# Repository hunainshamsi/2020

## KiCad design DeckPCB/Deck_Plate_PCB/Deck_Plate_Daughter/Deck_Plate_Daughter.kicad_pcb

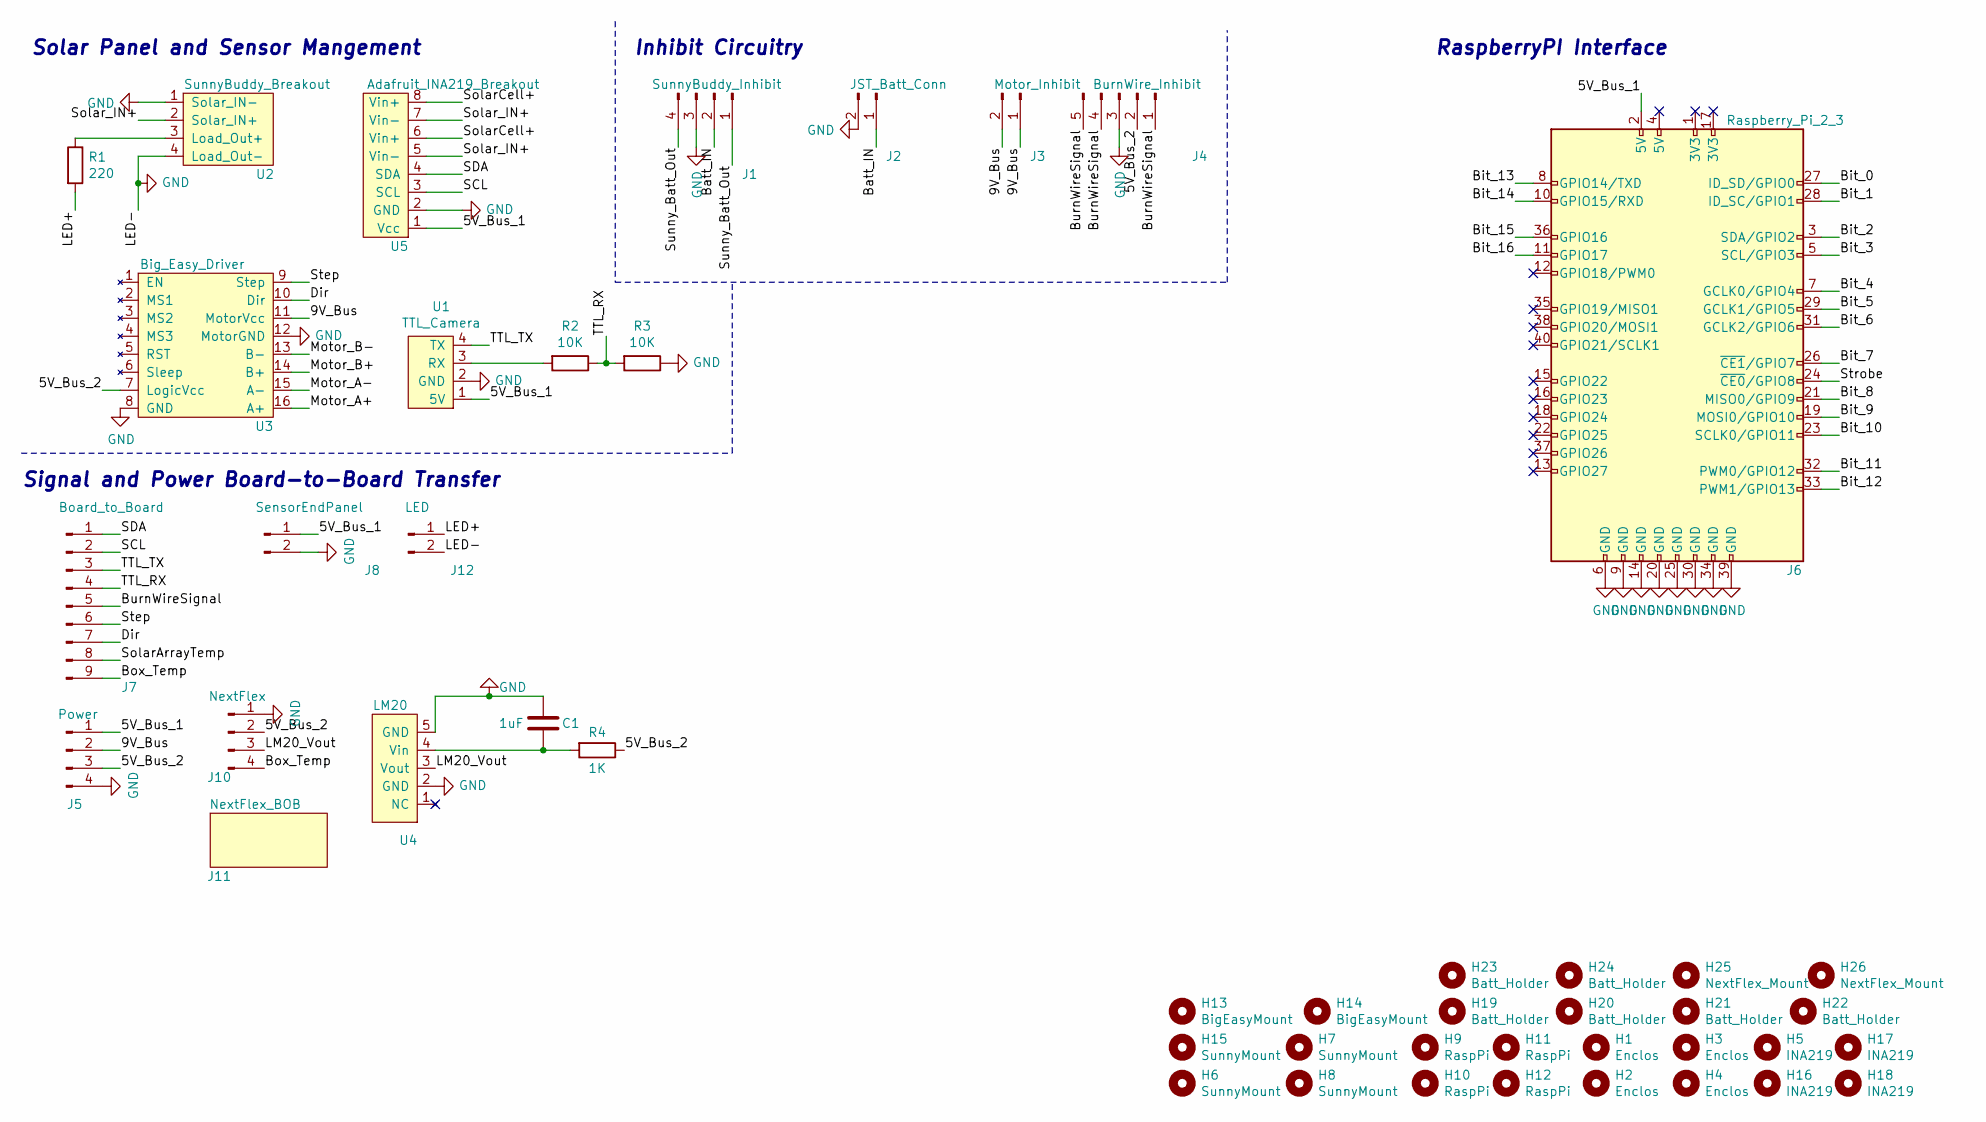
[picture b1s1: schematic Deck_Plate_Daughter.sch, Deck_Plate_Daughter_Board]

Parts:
C1: 1uF; C_Axial_L3.8mm_D2.6mm_P7.50mm_Horizontal
H1, H2, H3, H4: Enclos; MountingHole_3.5mm
H5, H16, H17, H18: INA219; Accel_MountingHole_2.5mm
H6, H7, H8, H15: SunnyMount; Accel_MountingHole_2.5mm
H9, H10, H11, H12: RaspPi; MountingHole_2.5mm
H13, H14: BigEasyMount; BigEasy_MountingHole_3.2mm_M3
H19, H20, H21, H22, H23, H24: Batt_Holder; MountingHole_5.3mm_M5
H25, H26: NextFlex_Mount; NextFlex_Mount_3mm
J1: SunnyBuddy_Inhibit; PinHeader_1x04_P2.54mm_Vertical
J2: JST_Batt_Conn; JST_PH_B2B-PH-K_1x02_P2.00mm_Vertical
J3: Motor_Inhibit; PinHeader_1x02_P2.54mm_Vertical
J4: BurnWire_Inhibit; PinHeader_1x05_P2.54mm_Vertical
J5: Power; PinHeader_1x04_P2.54mm_Vertical
J6: Raspberry_Pi_2_3; PinHeader_2x20_P2.54mm_Vertical
J7: Board_to_Board; PinHeader_1x09_P2.54mm_Vertical
J8: SensorEndPanel; PinHeader_1x02_P2.54mm_Vertical
J10: NextFlex; PinHeader_1x04_P2.54mm_Vertical
J11: NextFlex_BOB; NextFlex
J12: LED; PinHeader_1x02_P2.54mm_Vertical
R1: 220; R_Axial_DIN0207_L6.3mm_D2.5mm_P10.16mm_Horizontal
R2, R3: 10K; R_Axial_DIN0207_L6.3mm_D2.5mm_P10.16mm_Horizontal
R4: 1K; R_Axial_DIN0207_L6.3mm_D2.5mm_P10.16mm_Horizontal
U1: TTL_Camera; PinHeader_1x04_P2.54mm_Vertical
U2: SunnyBuddy_Breakout
U3: Big_Easy_Driver
U4: LM20; SOT-353_SC-70-5_Handsoldering
U5: Adafruit_INA219_Breakout; Adafruit_INA219_Breakout_header

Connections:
/5V_Bus_1: J5.1, J6.2 (5V), J8.1, U1.1 (5V), U5.1 (Vcc)
/5V_Bus_2: J4.2, J5.3, J10.2, R4.1, U3.7 (LogicVcc)
/9V_Bus: J3.1, J3.2, J5.2, U3.11 (MotorVcc)
/Batt_IN: J1.2, J2.1
/Bit_0: J6.27 (ID_SD/GPIO0)
/Bit_1: J6.28 (ID_SC/GPIO1)
/Bit_2: J6.3 (SDA/GPIO2)
/Bit_3: J6.5 (SCL/GPIO3)
/Bit_4: J6.7 (GCLK0/GPIO4)
/Bit_5: J6.29 (GCLK1/GPIO5)
/Bit_6: J6.31 (GCLK2/GPIO6)
/Bit_7: J6.26 (~CE1~/GPIO7)
/Bit_8: J6.21 (MISO0/GPIO9)
/Bit_9: J6.19 (MOSI0/GPIO10)
/Bit_10: J6.23 (SCLK0/GPIO11)
/Bit_11: J6.32 (PWM0/GPIO12)
/Bit_12: J6.33 (PWM1/GPIO13)
/Bit_13: J6.8 (GPIO14/TXD)
/Bit_14: J6.10 (GPIO15/RXD)
/Bit_15: J6.36 (GPIO16)
/Bit_16: J6.11 (GPIO17)
/Box_Temp: J7.9, J10.4
/BurnWireSignal: J4.1, J4.4, J4.5, J7.5
/Dir: J7.7, U3.10 (Dir)
/LED+: J12.1, R1.2
/LM20_Vout: J10.3, U4.3 (Vout)
/Motor_A+: U3.16 (A+)
/Motor_A-: U3.15 (A-)
/Motor_B+: U3.14 (B+)
/Motor_B-: U3.13 (B-)
/SCL: J7.2, U5.3 (SCL)
/SDA: J7.1, U5.4 (SDA)
/SolarArrayTemp: J7.8
/SolarCell+: U5.6 (Vin+), U5.8 (Vin+)
/Solar_IN+: U2.2 (Solar_IN+), U5.5 (Vin-), U5.7 (Vin-)
/Step: J7.6, U3.9 (Step)
/Strobe: J6.24 (~CE0~/GPIO8)
/Sunny_Batt_Out: J1.1, J1.4
/TTL_RX: J7.4, R2.1, R3.2
/TTL_TX: J7.3, U1.4 (TX)
GND: C1.2, J1.3, J2.2, J4.3, J5.4, J6.6 (GND), J6.9 (GND), J6.14 (GND), J6.20 (GND), J6.25 (GND), J6.30 (GND), J6.34 (GND), J6.39 (GND), J8.2, J10.1, J12.2, R3.1, U1.2 (GND), U2.1 (Solar_IN-), U2.4 (Load_Out-), U3.8 (GND), U3.12 (MotorGND), U4.2 (GND), U4.5 (GND), U5.2 (GND)
unnamed: C1.1, R4.2, U4.4 (Vin)
unnamed: R1.1, U2.3 (Load_Out+)
unnamed: R2.2, U1.3 (RX)

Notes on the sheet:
Inhibit Circuitry
Solar Panel and Sensor Mangement
Signal and Power Board-to-Board Transfer
RaspberryPI Interface

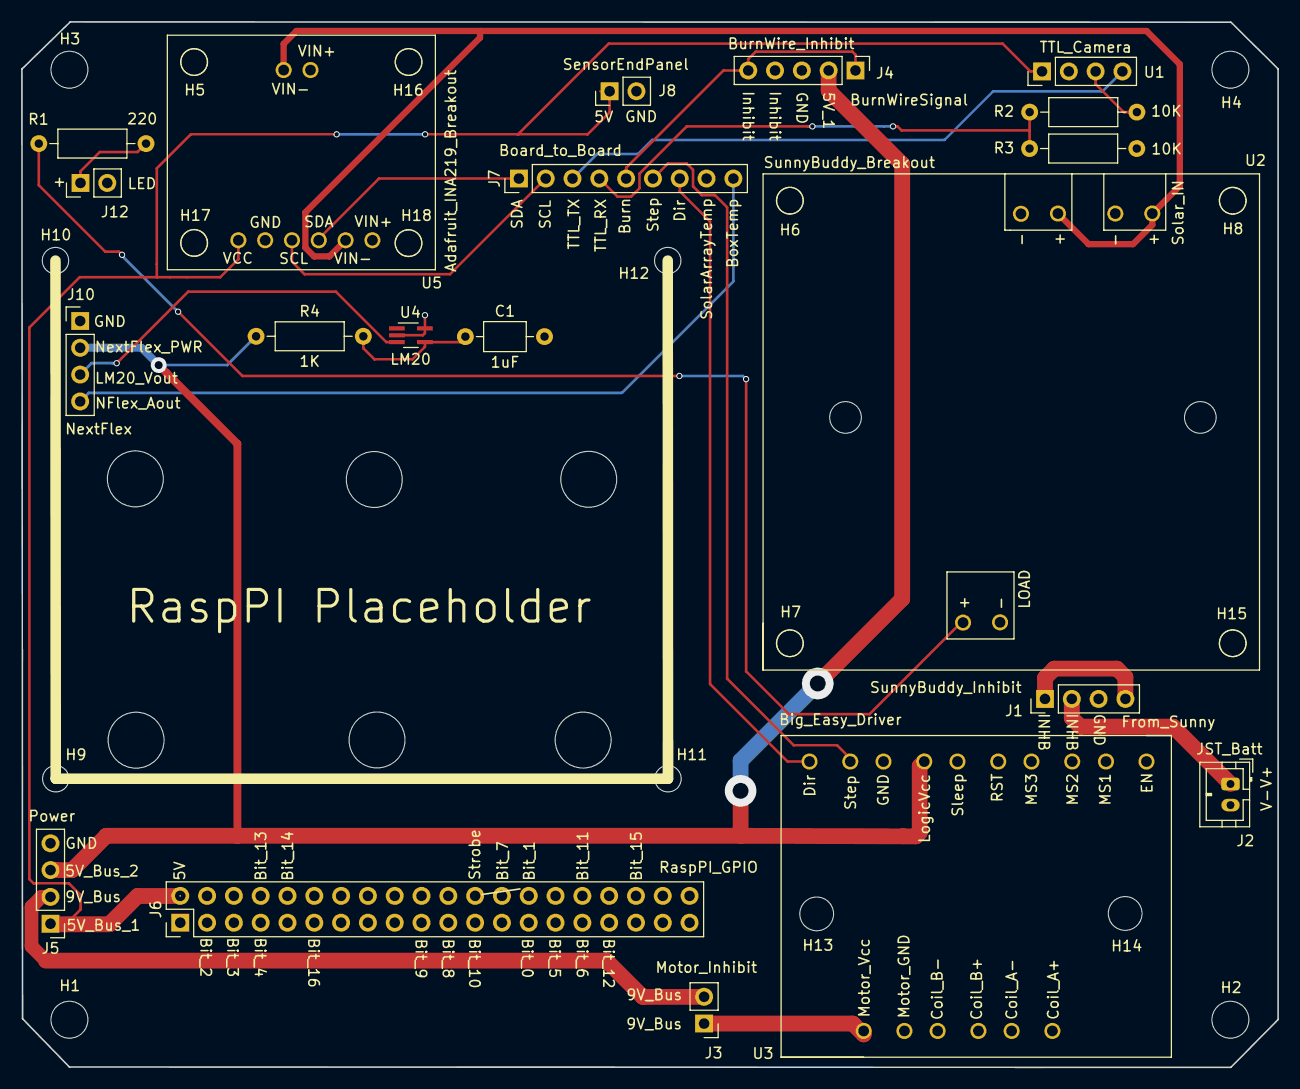
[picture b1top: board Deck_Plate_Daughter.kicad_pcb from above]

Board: 2 copper layers, 119.0 x 99.1 mm, 47 parts (0 on the bottom side), 21 nets.

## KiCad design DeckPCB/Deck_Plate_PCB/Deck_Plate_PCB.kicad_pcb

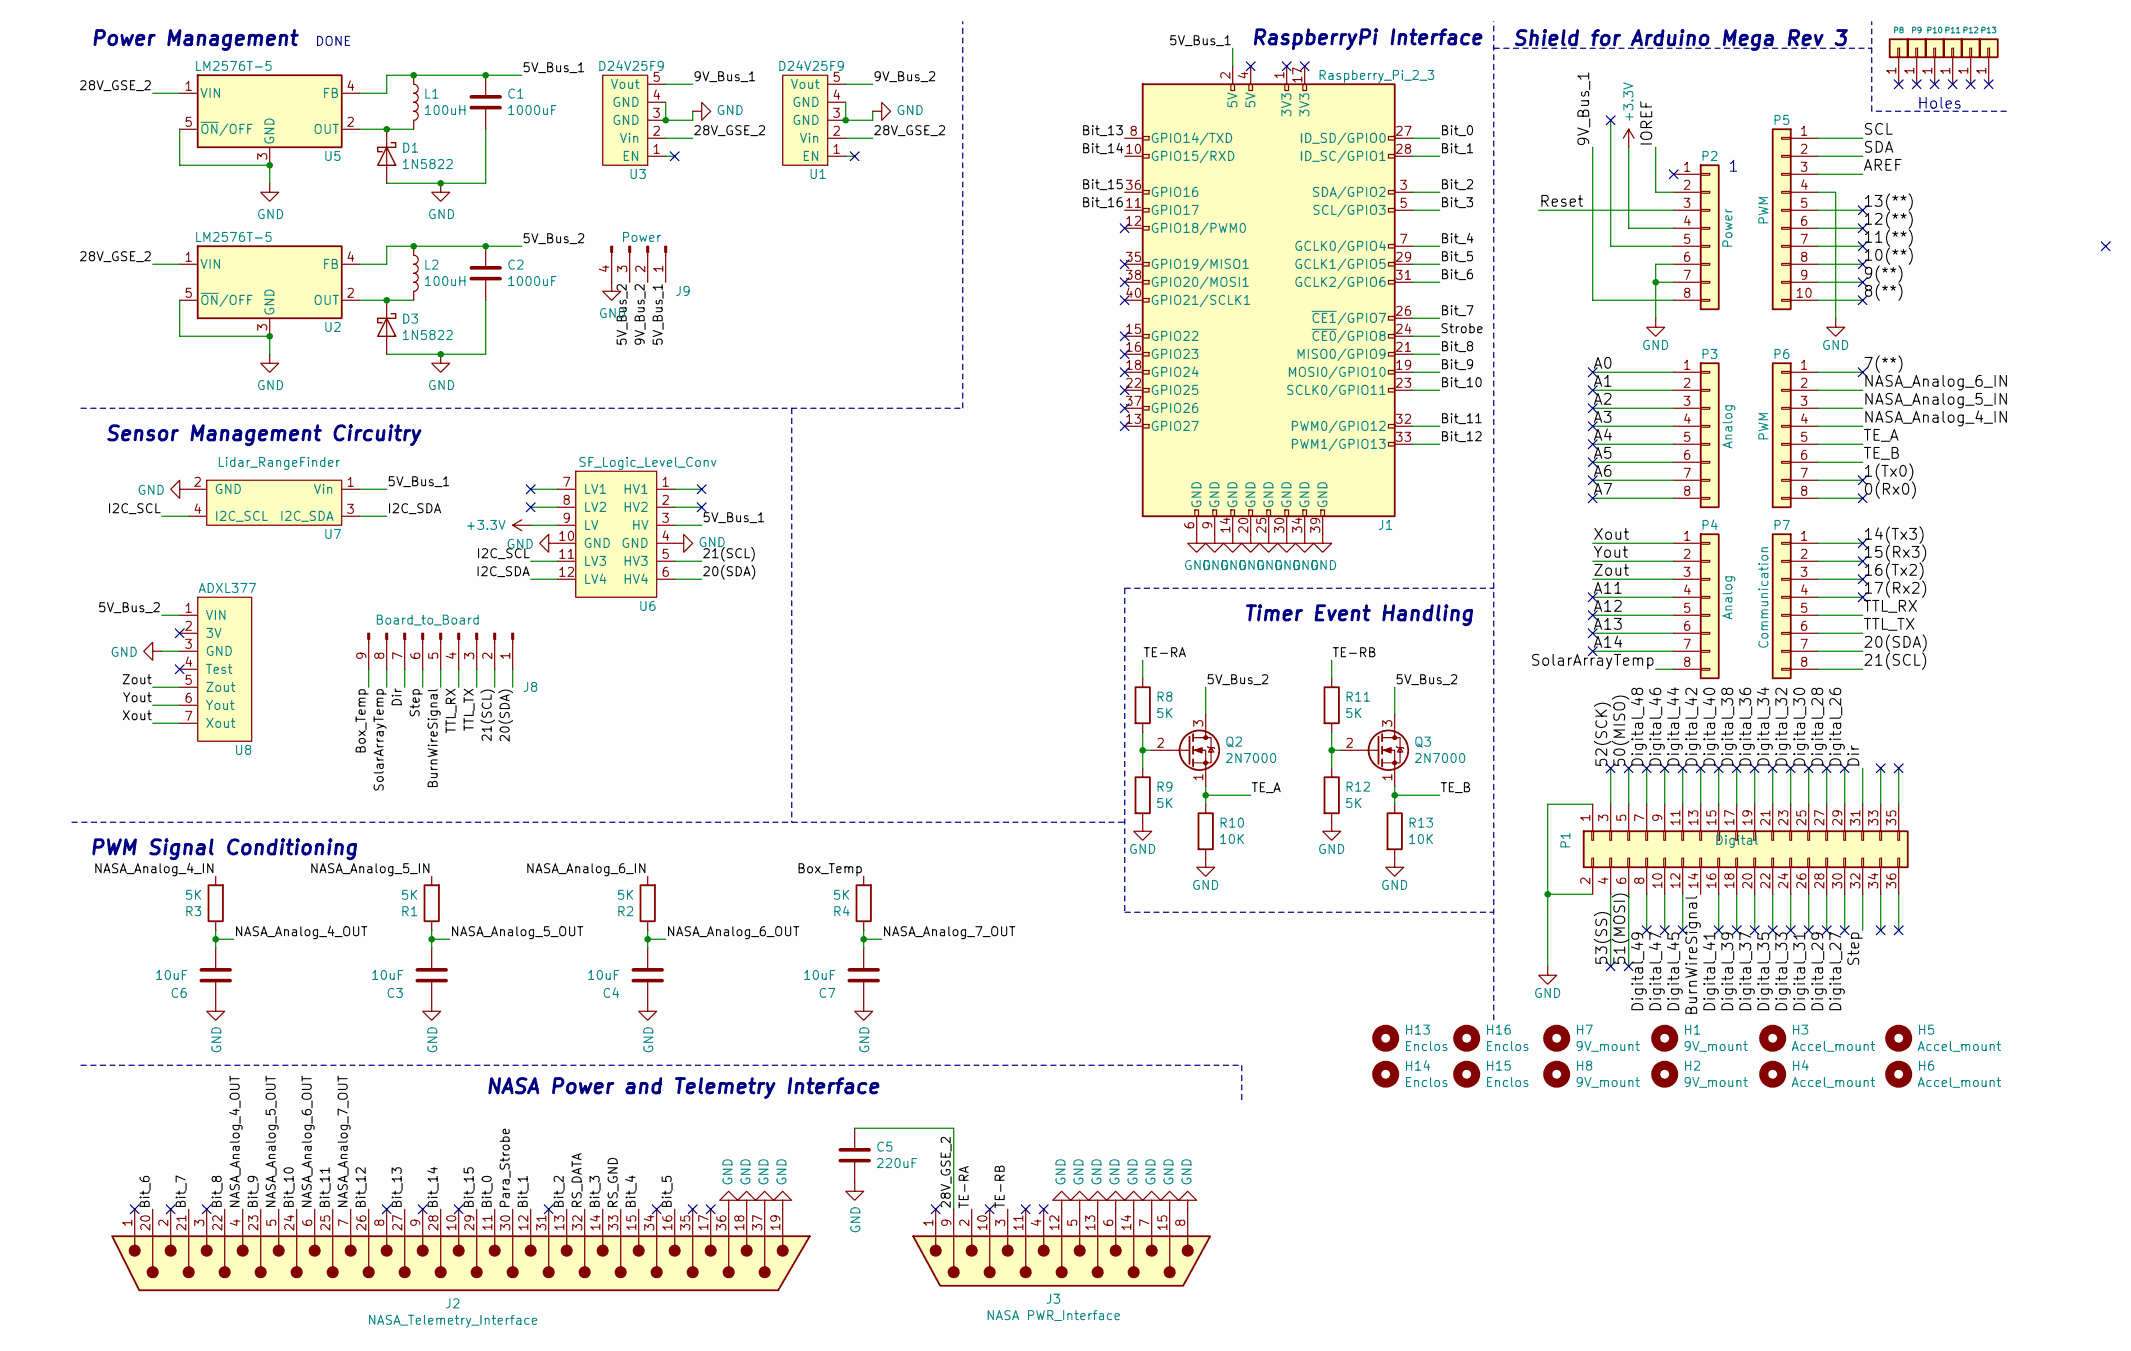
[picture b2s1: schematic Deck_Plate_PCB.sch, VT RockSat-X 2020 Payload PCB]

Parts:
C1, C2: 1000uF; 1000uF_Cap
C3, C4, C6, C7: 10uF; C_Axial_L3.8mm_D2.6mm_P7.50mm_Horizontal; Manufacture P/N FG24X7R1A106KRT06; DigiKey P/N 445-173370-1-ND
C5: 220uF; 220uF_Cap
D1, D3: 1N5822; D_DO-201AD_P12.70mm_Horizontal
H1, H2, H7, H8: 9V_mount; 9V_MountingHole_2.2mm
H3, H4, H5, H6: Accel_mount; Accel_MountingHole_2.5mm
H13, H14, H15, H16: Enclos; MountingHole_3.5mm
J1: Raspberry_Pi_2_3; PinHeader_2x20_P2.54mm_Vertical
J2: NASA_Telemetry_Interface; NASA_Telem_37-pin_DSub
J3: NASA PWR_Interface; NASA_PWR_15-pin_DSub
J8: Board_to_Board; PinHeader_1x09_P2.54mm_Vertical
J9: Power; PinHeader_1x04_P2.54mm_Vertical
L1, L2: 100uH; L_Toroid_Vertical_L21.6mm_W9.5mm_P7.11mm_Pulse_C
P1: Digital; Socket_Strip_Arduino_2x18
P2: Power; Socket_Strip_Arduino_1x08
P3, P4: Analog; Socket_Strip_Arduino_1x08
P5: PWM; Socket_Strip_Arduino_1x10
P6: PWM; Socket_Strip_Arduino_1x08
P7: Communication; Socket_Strip_Arduino_1x08
P8, P9, P10, P11, P12, P13: CONN_01X01; Arduino_1pin
Q2, Q3: 2N7000; TO-92_Inline
R1, R2, R3, R4, R8, R9, R11, R12: 5K; R_Axial_DIN0207_L6.3mm_D2.5mm_P10.16mm_Horizontal
R10, R13: 10K; R_Axial_DIN0207_L6.3mm_D2.5mm_P10.16mm_Horizontal; Manufacture P/N RNF14FTD10K0; DigiKey P/N RNF14FTD10K0CT-ND
U1, U3: D24V25F9
U2, U5: LM2576T-5; TO-220-5_Vertical
U6: SF_Logic_Level_Conv
U7: Lidar_RangeFinder; PinHeader_1x04_P2.54mm_Vertical
U8: ADXL377; ADXL337

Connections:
+3V3: P2.4, U6.9 (LV)
/0(Rx0): P6.8
/1(Tx0): P6.7
/5V_Bus_1: C1.1, J1.2 (5V), J9.1, L1.1, U5.4 (FB), U6.3 (HV), U7.1 (Vin)
/5V_Bus_2: C2.1, J9.3, L2.1, Q2.3 (D), Q3.3 (D), U2.4 (FB), U8.1 (VIN)
/7(**): P6.1
/8(**): P5.10
/9(**): P5.9
/9V_Bus_1: P2.8, U3.5 (Vout)
/9V_Bus_2: J9.2, U1.5 (Vout)
/10(**): P5.8
/11(**): P5.7
/12(**): P5.6
/13(**): P5.5
/14(Tx3): P7.1
/15(Rx3): P7.2
/16(Tx2): P7.3
/17(Rx2): P7.4
/20(SDA): J8.1, P7.7, U6.6 (HV4)
/21(SCL): J8.2, P7.8, U6.5 (HV3)
/28V_GSE_2: C5.1, J3.9, U1.2 (Vin), U2.1 (VIN), U3.2 (Vin), U5.1 (VIN)
/50(MISO): P1.5
/51(MOSI): P1.6
/52(SCK): P1.3
/53(SS): P1.4
/A0: P3.1
/A1: P3.2
/A2: P3.3
/A3: P3.4
/A4: P3.5
/A5: P3.6
/A6: P3.7
/A7: P3.8
/A11: P4.4
/A12: P4.5
/A13: P4.6
/A14: P4.7
/AREF: P5.3
/Bit_0: J1.27 (ID_SD/GPIO0), J2.11
/Bit_1: J1.28 (ID_SC/GPIO1), J2.12
/Bit_2: J1.3 (SDA/GPIO2), J2.13
/Bit_3: J1.5 (SCL/GPIO3), J2.14
/Bit_4: J1.7 (GCLK0/GPIO4), J2.15
/Bit_5: J1.29 (GCLK1/GPIO5), J2.16
/Bit_6: J1.31 (GCLK2/GPIO6), J2.20
/Bit_7: J1.26 (~CE1~/GPIO7), J2.21
/Bit_8: J1.21 (MISO0/GPIO9), J2.22
/Bit_9: J1.19 (MOSI0/GPIO10), J2.23
/Bit_10: J1.23 (SCLK0/GPIO11), J2.24
/Bit_11: J1.32 (PWM0/GPIO12), J2.25
/Bit_12: J1.33 (PWM1/GPIO13), J2.26
/Bit_13: J1.8 (GPIO14/TXD), J2.27
/Bit_14: J1.10 (GPIO15/RXD), J2.28
/Bit_15: J1.36 (GPIO16), J2.29
/Bit_16: J1.11 (GPIO17)
/Box_Temp: J8.9, R4.2
/BurnWireSignal: J8.5, P1.14
/Digital_26: P1.29
/Digital_27: P1.30
/Digital_28: P1.27
/Digital_29: P1.28
/Digital_30: P1.25
/Digital_31: P1.26
/Digital_32: P1.23
/Digital_33: P1.24
/Digital_34: P1.21
/Digital_35: P1.22
/Digital_36: P1.19
/Digital_37: P1.20
/Digital_38: P1.17
/Digital_39: P1.18
/Digital_40: P1.15
/Digital_41: P1.16
/Digital_42: P1.13
/Digital_44: P1.11
/Digital_45: P1.12
/Digital_46: P1.9
/Digital_47: P1.10
/Digital_48: P1.7
/Digital_49: P1.8
/Dir: J8.7, P1.31
/I2C_SCL: U6.11 (LV3), U7.4 (I2C_SCL)
/I2C_SDA: U6.12 (LV4), U7.3 (I2C_SDA)
/IOREF: P2.2
/NASA_Analog_4_IN: P6.4, R3.2
/NASA_Analog_4_OUT: C6.2, J2.4, R3.1
/NASA_Analog_5_IN: P6.3, R1.2
/NASA_Analog_5_OUT: C3.2, J2.5, R1.1
/NASA_Analog_6_IN: P6.2, R2.2
/NASA_Analog_6_OUT: C4.2, J2.6, R2.1
/NASA_Analog_7_OUT: C7.2, J2.7, R4.1
/Para_Strobe: J2.30
/RS_DATA: J2.32
/RS_GND: J2.33
/Reset: P2.3
/SCL: P5.1
/SDA: P5.2
/SolarArrayTemp: J8.8, P4.8
/Step: J8.6, P1.32
/Strobe: J1.24 (~CE0~/GPIO8)
/TE-RA: J3.2, R8.1
/TE-RB: J3.3, R11.1
/TE_A: P6.5, Q2.1 (S), R10.1
/TE_B: P6.6, Q3.1 (S), R13.1
/TTL_RX: J8.4, P7.5
/TTL_TX: J8.3, P7.6
/Xout: P4.1, U8.7 (Xout)
/Yout: P4.2, U8.6 (Yout)
/Zout: P4.3, U8.5 (Zout)
GND: C1.2, C2.2, C3.1, C4.1, C5.2, C6.1, C7.1, D1.2 (A), D3.2 (A), J1.6 (GND), J1.9 (GND), J1.14 (GND), J1.20 (GND), J1.25 (GND), J1.30 (GND), J1.34 (GND), J1.39 (GND), J2.18, J2.19, J2.36, J2.37, J3.5, J3.6, J3.7, J3.8, J3.12, J3.13, J3.14, J3.15, J9.4, P1.1, P1.2, P2.6, P2.7, P5.4, R9.2, R10.2, R12.2, R13.2, U1.3 (GND), U1.4 (GND), U2.3 (GND), U2.5 (~ON~/OFF), U3.3 (GND), U3.4 (GND), U5.3 (GND), U5.5 (~ON~/OFF), U6.4 (GND), U6.10 (GND), U7.2 (GND), U8.3 (GND)
unnamed: D1.1 (K), L1.2, U5.2 (OUT)
unnamed: D3.1 (K), L2.2, U2.2 (OUT)
unnamed: Q2.2 (G), R8.2, R9.1
unnamed: Q3.2 (G), R11.2, R12.1

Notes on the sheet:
Shield for Arduino Mega Rev 3
Holes
Power Management
Sensor Management Circuitry
NASA Power and Telemetry Interface
Timer Event Handling
DONE
RaspberryPi Interface
PWM Signal Conditioning

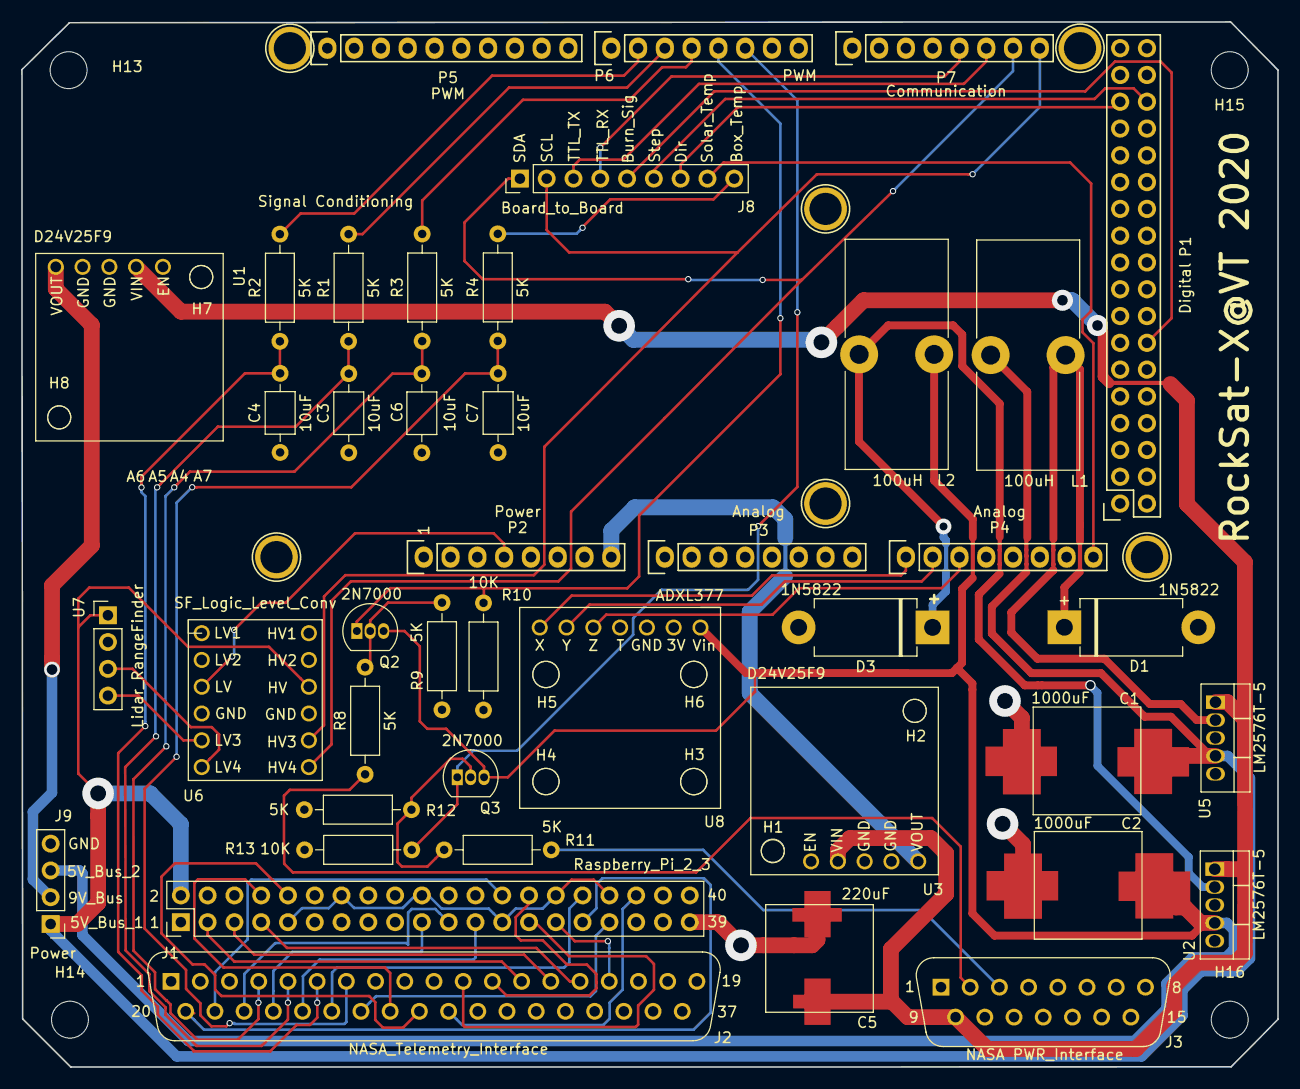
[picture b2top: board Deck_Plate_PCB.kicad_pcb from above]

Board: 2 copper layers, 119.1 x 99.1 mm, 60 parts (0 on the bottom side), 52 nets.

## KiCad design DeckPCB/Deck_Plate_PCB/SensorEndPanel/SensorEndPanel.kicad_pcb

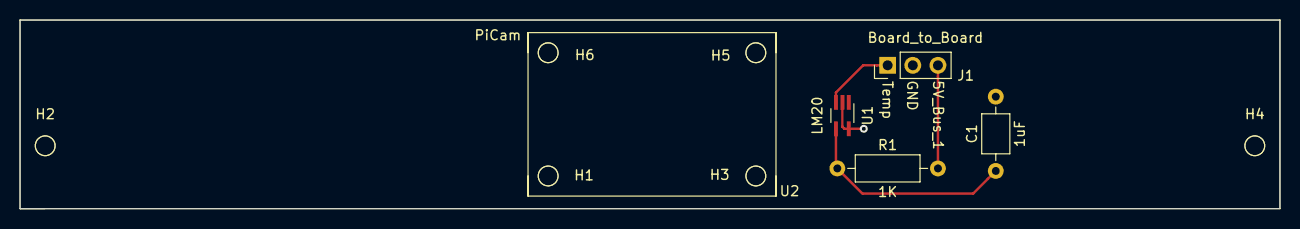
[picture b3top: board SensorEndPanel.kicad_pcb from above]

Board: 2 copper layers, 127.3 x 19.1 mm, 11 parts (0 on the bottom side), 4 nets.

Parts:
C1: 1uF; C_Axial_L3.8mm_D2.6mm_P7.50mm_Horizontal
H1, H2, H3, H4, H5, H6: MountingHole; MountingHole_2mm
J1: Board_to_Board; PinHeader_1x03_P2.54mm_Vertical
R1: 1K; R_Axial_DIN0207_L6.3mm_D2.5mm_P10.16mm_Horizontal
U1: LM20; SOT-353_SC-70-5_Handsoldering
U2: PiCam

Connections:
/5V_Bus_1: J1.3, R1.2
/SolarArrayTemp: J1.1, U1.3
GND: C1.2, J1.2, U1.2, U1.5
unnamed: C1.1, R1.1, U1.4

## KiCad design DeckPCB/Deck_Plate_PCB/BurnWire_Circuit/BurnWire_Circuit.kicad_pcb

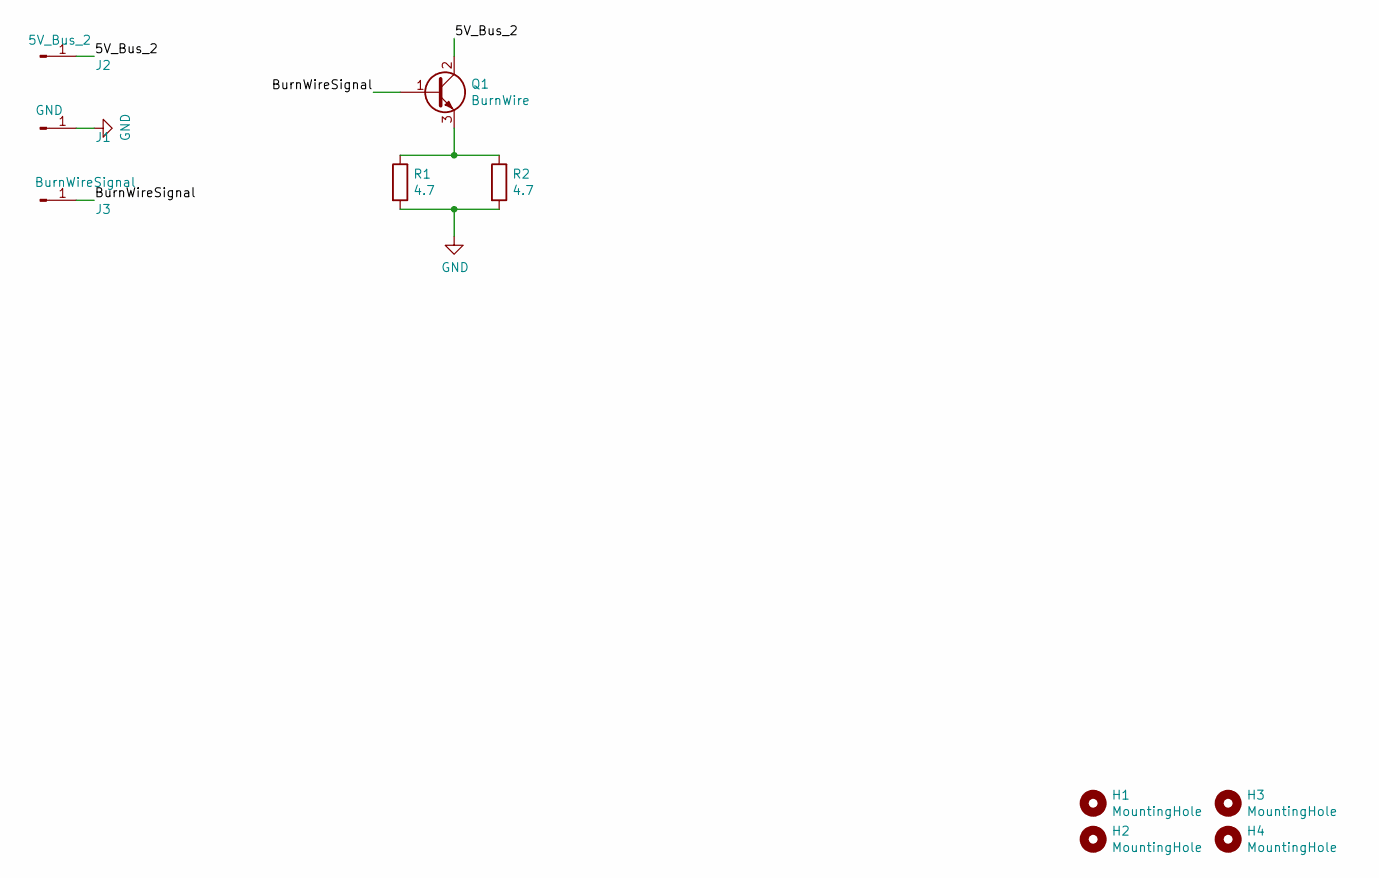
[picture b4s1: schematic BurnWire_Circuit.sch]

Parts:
H1, H2, H3, H4: MountingHole; MountingHole_3.2mm_M3
J1: GND; Terminal_Lug_PCB
J2: 5V_Bus_2; Terminal_Lug_PCB
J3: BurnWireSignal; Terminal_Lug_PCB
Q1: BurnWire; TO-251-3_Vertical
R1, R2: 4.7; R_Axial_DIN0207_L6.3mm_D2.5mm_P10.16mm_Horizontal

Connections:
/5V_Bus_2: J2.1, Q1.2 (C)
/BurnWireSignal: J3.1, Q1.1 (B)
GND: J1.1, R1.2, R2.2
unnamed: Q1.3 (E), R1.1, R2.1

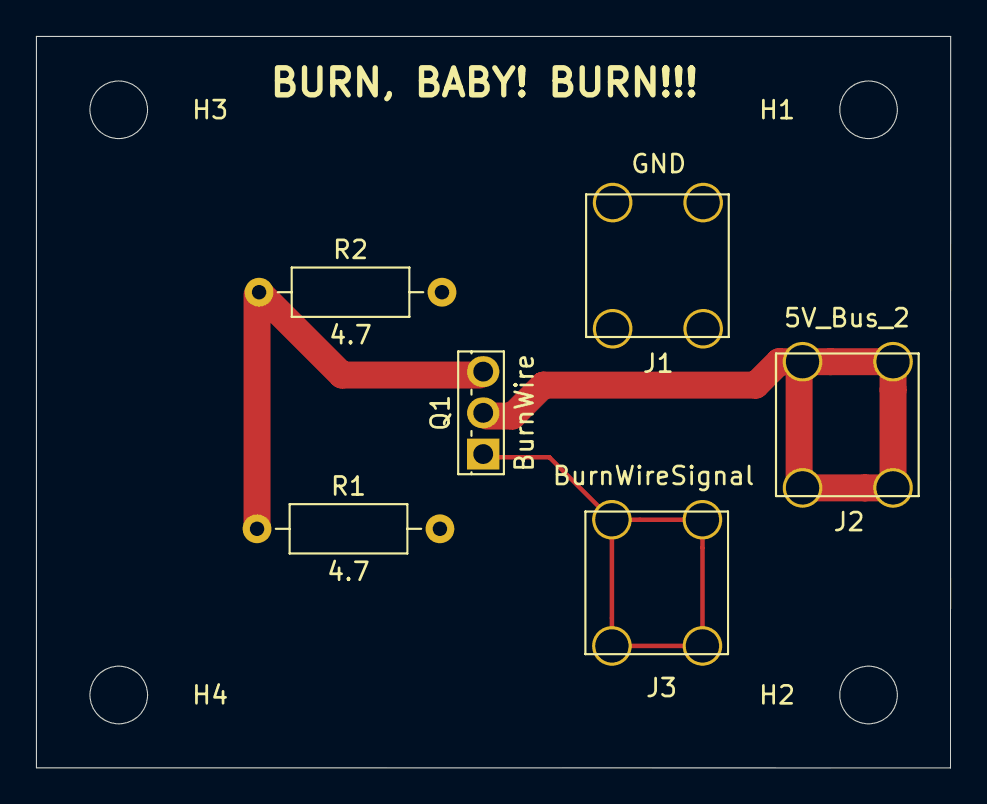
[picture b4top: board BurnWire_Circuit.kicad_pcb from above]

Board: 2 copper layers, 50.8 x 40.6 mm, 10 parts (0 on the bottom side), 4 nets.

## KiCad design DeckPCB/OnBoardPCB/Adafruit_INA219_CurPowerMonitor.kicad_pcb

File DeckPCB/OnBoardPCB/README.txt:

Things that need to be fixed
-ArduinoMegaDigital2 (U27) pin 4 Timer Events connection needs to be added to the other set of digital pins on the Mega.
	This 36 pin connection will need to be added. Maybe all digital pins used can be changed to using this one 36 pin section?
-Add pins for raspberry pi connections for TTL Serial Camera. You wont need to add all of the raspberry pi pins, just pins 8 and 10.
-The Big Easy Driver pcb through holes have been added, but the board will need to be expanded to fit all of the things
-All footprints for the capacitors, reistors, transistors, etc need to be double checked with the footprints of the parts that are going to be ordered.

Things to note
-Raspberry Pi probably should be on top to allow for ribbon cable connection, then PCB, then arduino mega on bottom?
-SunnyBuddy is huge, and might want to mount it separately to allow for a smaller pcb. Same with some of the other ones.

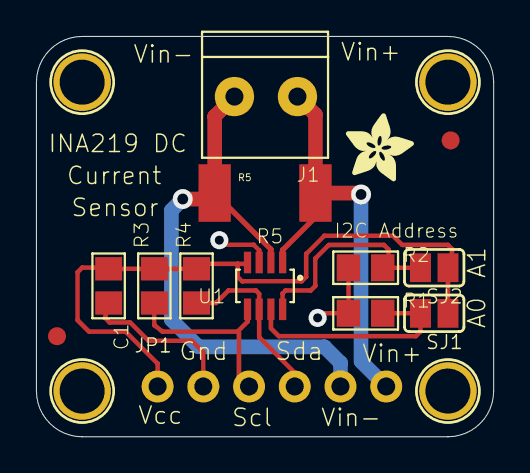
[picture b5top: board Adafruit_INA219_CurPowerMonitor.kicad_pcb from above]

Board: 2 copper layers, 25.4 x 22.2 mm, 18 parts (0 on the bottom side), 8 nets.

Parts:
C1: 0.1µF; 0805
FID1, FID2: FIDUCIAL; FIDUCIAL_1MM
J1: TERMBLOCK_1X2-3.5MM; 1X2-3.5MM
JP1: HEADER-1X670MIL; 1X06_ROUND_70
R1, R2, R3, R4: 10K; 0805
R5: 0.1/1% (PT2512FK-070R1L); 2512
SJ1, SJ2: SOLDERJUMPERREFLOW_NOPASTE; SOLDERJUMPER_REFLOW_NOPASTE
U1: INA219BIDCNT; SOT23-8
U$7, U$8, U$9, U$10: MOUNTINGHOLE2.5; MOUNTINGHOLE_2.5_PLATED
U$11: ADAFRUIT_3.5MM

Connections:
/SCL: JP1.3, R3.1, U1.5
/SDA: JP1.4, R4.1, U1.6
/VIN+: J1.2, JP1.6, R5.2, U1.1
/VIN-: J1.1, JP1.5, R5.1, U1.2
GND: C1.2, JP1.2, R1.1, R2.1, U1.3
unnamed: R1.2, SJ1.2, U1.7
unnamed: R2.2, SJ2.2, U1.8
VCC: C1.1, JP1.1, R3.2, R4.2, SJ1.1, SJ2.1, U1.4

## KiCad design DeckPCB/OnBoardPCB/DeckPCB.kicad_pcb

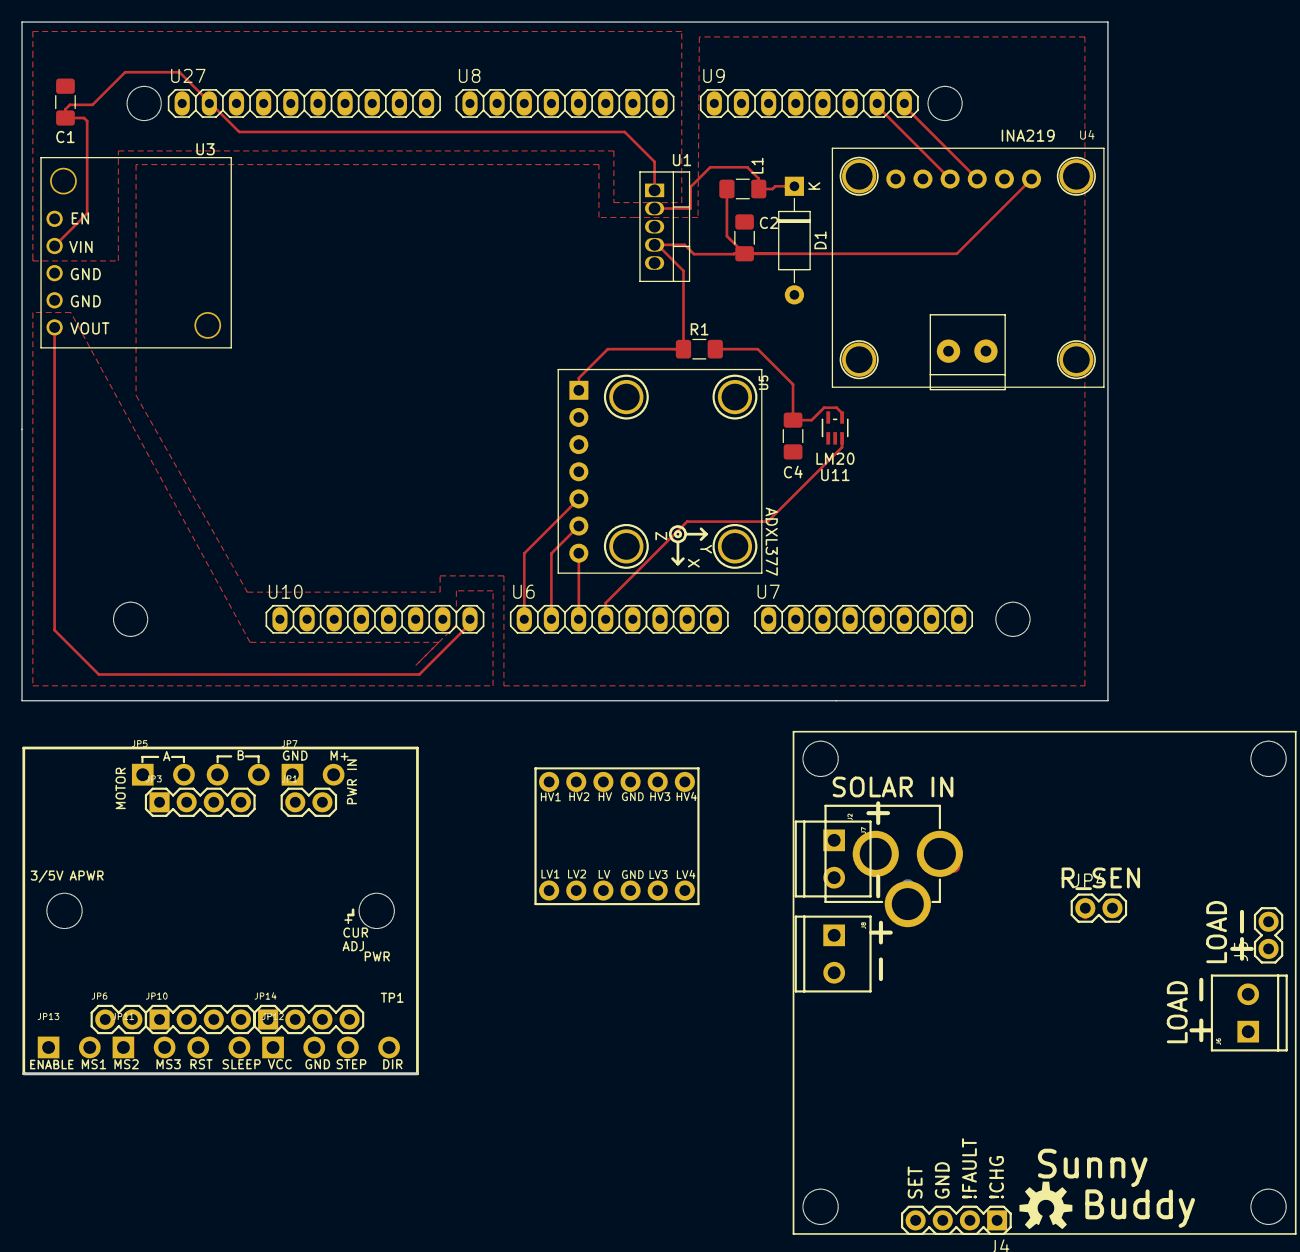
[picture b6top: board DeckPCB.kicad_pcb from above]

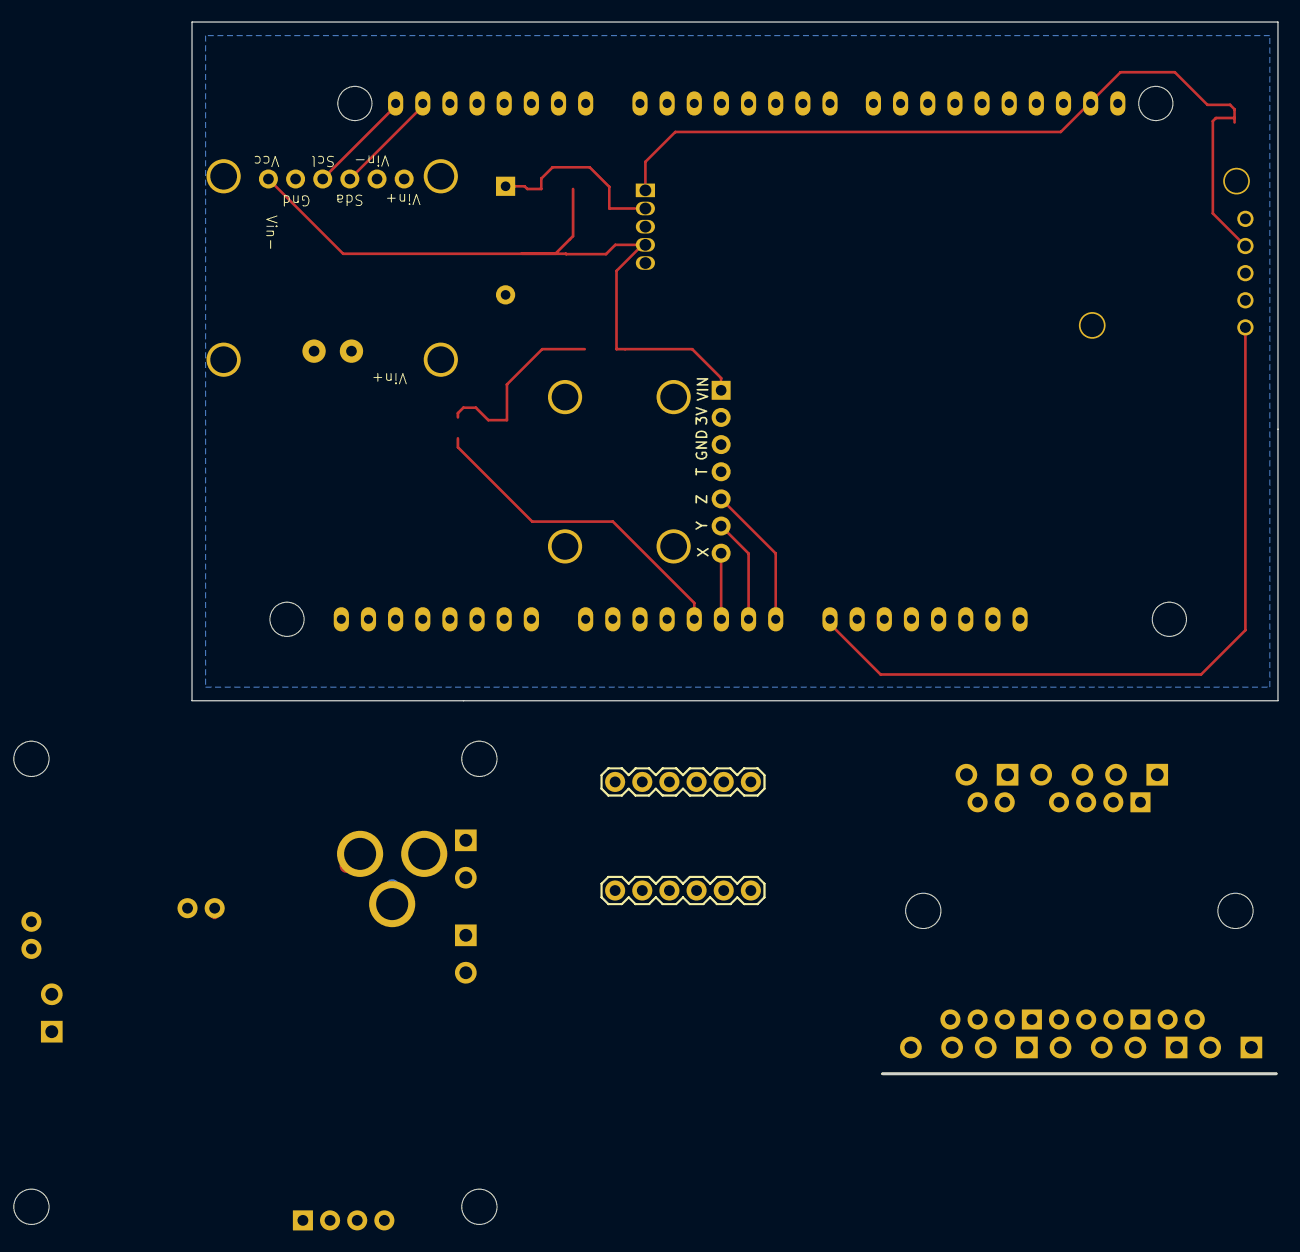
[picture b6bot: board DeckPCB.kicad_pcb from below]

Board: 2 copper layers, 101.6 x 98.4 mm, 57 parts (2 on the bottom side), 13 nets.

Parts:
 : INA219
 #2,  #3,  #5: MOUNTINGHOLE_2.5_PLATED
 #4: 1X2-3.5MM
C1: 220uF; C_1206_3216Metric_Pad1.42x1.75mm_HandSolder
C2: 1000uF; C_1206_3216Metric_Pad1.42x1.75mm_HandSolder
C4: 1uF; C_1206_3216Metric_Pad1.42x1.75mm_HandSolder
D1: 1N5822; D_A-405_P10.16mm_Horizontal
J2: POWER_JACKPTH; POWER_JACK_PTH
J4: M04PTH; 1X04
J5: M02PTH; 1X02
J6, J7, J8: M023.5MM; SCREWTERMINAL-3.5MM-2
JP1, JP2: M06SIP; 1X06
JP1#2, JP6: M02PTH; 1X02
JP3, JP10, JP14: M04PTH; 1X04
JP4: R_SEN; 1X02
JP5, JP11, JP12: M04SCREW_LOCK; SCREWTERMINAL-3.5MM-4_LOCK
JP7, JP13: M023.5MM_LOCK; SCREWTERMINAL-3.5MM-2_LOCK
JP8, JP9: STAND-OFF
L1: 100uH; L_1206_3216Metric_Pad1.42x1.75mm_HandSolder
LOGO2: OSHW-LOGOM; OSHW-LOGO-M
MH1, MH2, MH3, MH4: MountingHole_3.2mm_M3
R1: 1K; R_1206_3216Metric_Pad1.42x1.75mm_HandSolder
STANDOFF1, STANDOFF2, STANDOFF3, STANDOFF4: STAND-OFF
U1: LM2576T-5; TO-220-5_Vertical
U3: D24V25F9
U4: INA219
U5: ADXL377
U6: ArduinoMegaAnalog1; HeaderPins8
U7: ArduinoMegaAnalog2; HeaderPins8
U8: ArduinoMegaDigital; HeaderPins8
U9: ArduinoMegaCommunication; HeaderPins8
U10: ArduinoMegaPower; HeaderPins8
U11: LM20
U27: ArduinoMegaDigital2; HeaderPins10
U$2, U$3, U$7, U$8, U$9: MOUNTINGHOLE_2.5_PLATED

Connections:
+28V: C1.1, U1.1, U3.2
/5V: C2.1, L1.2, R1.1, U1.4, U4.1, U5.1
/9V: U3.5, U10.8
/DeployCheck: U27.5, U27.6
/PayloadTemp: U6.4, U11.3
/Scl: U4.3, U9.8
/Sda: U4.4, U9.7
/XAnalog: U5.7, U6.3
/YAnalog: U5.6, U6.2
/ZAnalog: U5.5, U6.1
GND: C1.2, C2.2, C4.2, D1.2, U1.3, U1.5, U3.3, U3.4, U4.2, U5.3, U11.2, U11.5
unnamed: C4.1, R1.2, U11.4
unnamed: D1.1, L1.1, U1.2

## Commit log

2019-10-20 Add files via upload
    Uploaded files for generating performance estimates and performance analysis
2019-10-27 Add files via upload
    Updates to solar panel analysis MATLAB code
2019-11-19 preliminary ideas for control loop
2019-12-01 serial connection up and running, transmitting real data for incidence angle detection with opencv running on pi
2019-12-04 realtime opencv running with pi camera at 30 fps, saving video. need to fix frame rate when saving video because we can't really process at 30fps...
2019-12-06 updated control software for adruino to match flowchart and opencv should be more robust
2020-01-02 Create gitkeep
2020-01-15 Create garbage
2020-01-20 Creating a TEST README file to confirm GIT command line is working
2020-01-25 Website update part 1 - Nicholas Jones
2020-01-25 Website update part 2 - Nicholas Jones
2020-02-01 much cleaner, class based python control loop... should be ready for integration testing once we throw the telemetry code in, will be crucial to see if timing is good enough, otherwise will need to b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
2020-02-02 Uploading test code for the range finder
    Link to rangefinder library: https://github.com/garmin/LIDARLite_Arduino_Library
2020-02-06 Added new PCB project directory called Deck_Plate_PCB, this new directory represents the current working PCB files, KiCAD symbols, KiCAD footprints, and layout. BEFORE MAKING ANY EDITS SEE (Kris Ston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
2020-02-06 Lots of new telemetry code and resources. All functions currently finished are in the TelemLoop.py file
2020-02-13 need to commit this because if I lose it ill cry.
2020-02-13 phew... took forever but TTL camera is connected through Arduino serial1 and transmits hex jpg to pi via serial link... don't ask
2020-02-13 cleaning
2020-02-13 ok last one: images now roll in sequentially, need to slow this down so datarate is faster than framerate, and need to account for potential crash if python script starts during frame transfer and de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
2020-02-19 Deleted OnBoardPCB folder, replaced with Deck_Plate_PCB. This should be treated as the MASTER PCB reference from here on out. Added all sensor footprints and symbols as custom parts which are part of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
2020-02-21 All sensors work except unimplemented rangefinder
2020-02-21 move
2020-02-21 all sensors work!
2020-02-23 Finished all symbol and footprint additions. Added mounting holes for SunnyBuddy, INA219, and ADXL377. Added discrete component footprints. Defined NASA PWR and TELEMETRY pinouts.
2020-02-24 Updated RaspPi connections based on input from Software. Updated footprints from capacitor and inductor changes. Added inhibit header for batter, motor, and burn-wire.
2020-02-25 gitignore - this should help
2020-02-27 Assigned signals between arduino and sensors based on software input.
2020-02-27 Updated connections to Logic Level Shifter and LiDAR sensor. Updated inhibit connection scheme.
2020-02-29 Initial PCB component placement finished. All mounting holes in place. NOT REPRESENTED: SunnyBuddy, INA219, Electrical inhibits, Motor circuitry, sensor end-panel circuitry. Will create daughter boar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
2020-03-01 Created new daughter board for SunnyBuddy and RaspPi. Initial component layout complete.
2020-03-03 Started routing of Deck_Plate_PCB, the main board.
2020-03-05 Finised routing fro Main_Board, Daughter_Board, and BurnWire circuits. Creating SensorEndPanel board next.
2020-03-06 updated PCB routing and creation of BurnWire circuit board and updated Daughter_Board
2020-03-18 Added signal conditioning circuitry
2020-03-18 Added signal conditioning circuitry and finalized main deck PCB component placement and signal tracing
2020-03-24 Updated main board to incorporate all 16-bits of telemetry lines
2020-03-31 algo to calc incidence angle based on FOV... untested
2020-04-01 Updated PCB for NASA analog lines and signal conditioning circuitry. Added Gerber file ZIP for DECK_PLATE_MAIN
2020-04-01 Update with design reviews, sponsor logos, and 2020 pictures
2020-04-13 Updated Main_Deck_Plate and Daughter_Board to fit Electronics Enclosure internal dimensions. Created all PCB Gerber files. Created all PCB PNG images. Created all PCB STEP files for mechanical integr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
2020-04-13 Created PCB_Pics folder
2020-04-14 Updated Main_Board and Daughter_Board to have rounded off corners to fit inside of the Electronics Enclosure. Verified with CAD model of electronics enclosure.
2020-04-22 notes for nick
2020-04-26 Update control_software.ino
    Added Matt's code for the motorcontrol.
2020-05-01 Created PCB BOM list
2020-05-07 Kris final commit: Updated PCB BOM
2020-05-12 fixed ttl cam, config issue, curr/volt work, everything running off power supply
2020-05-13 interrupts appear to work, still no motor code
2020-05-14 added shell script so that multithreading works... don't use python bs
2020-05-15 plotting added, among other things
2020-05-23 FSMR code
2020-07-05 Create control_softwarenew.ino
    Added burn wire functionality.
2020-07-05 Update control_software.ino
    Added burn wire functionality

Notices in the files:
parts and their libraries:
Copyright 2016 Accelerated Designs. All rights reserved.
